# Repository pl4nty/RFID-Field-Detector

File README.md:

# RFID-Field-Detector  
  
## What is it?  
RFID-Field-Detector is an open source PCB the size of a credit card that is capable of detecting the field generated by a RFID reader and identify if it is a LF(125kHz) or HF/NFC(13.56MHz) reader.  
  
## Who made it, and why?  
Corey Harding, it is something neat to hand out to people, sort of like a business card.  
  
## How is it licensed?  
The hardware itself (KiCad and Fritzing files and Gerber) is licensed under Creative Commons Attribution-ShareAlike 3.0 Unported  
The SVG files fall under the MIT license  
  
## How can I modify it?  
Open `kicad/LF-HF-RFID-Detector.kicad_pro` in [KiCad](https://www.kicad.org/) 10 or later and modify whatever you wish provided you comply with the license stated above.  
The KiCad project was converted from `LF-HF-RFID-Detector.fzz`, which is kept for reference and can still be opened in Fritzing. The KiCad project has the PCB only; Fritzing's breadboard and schematic views were not converted.  
The place-file origin is the bottom-left corner of the board, as in Fritzing, so exported positions line up with `GERBER/positions.csv`.  
  
## Tuning  
Each antenna and its capacitors form a tuned circuit, and an LED only lights when the reader's frequency is near that circuit's resonance.  
- HF (13.56MHz): C6 (82pF) across the back coil (about 1.4uH). C7-C9 are left unfitted for small trims, e.g. a few pF. Do not fit nF parts here: 12nF across this coil tunes it to about 1.2MHz.  
- LF (125kHz): C1 and C2 in series, then C3-C5 in parallel, across the front coil (about 64uH). The fitted values total about 26nF, which tunes it to about 123kHz.  
  
## Will you help me?  
Maybe, but make sure you try first.  
  
## Is it available for sale?  
I have redesigned it as a commercial product and it is being manufactured and distributed by April Brother.  
Cost is sub $10.00 USD.  
Tindie: https://www.tindie.com/products/aprbrother/rfid-field-detector/

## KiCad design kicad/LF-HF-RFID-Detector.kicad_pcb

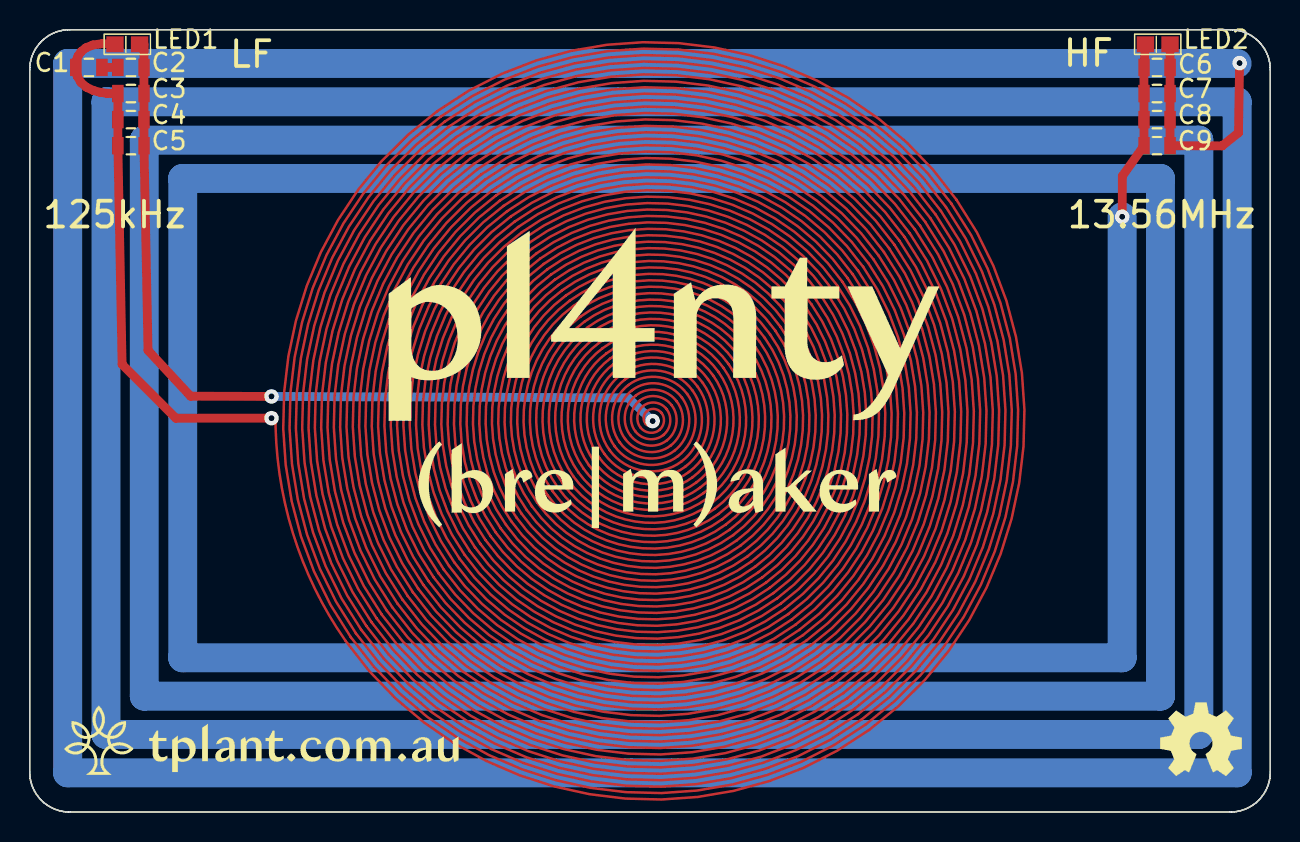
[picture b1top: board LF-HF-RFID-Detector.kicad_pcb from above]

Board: 2 copper layers, 85.6 x 54.0 mm, 11 parts (0 on the bottom side), 5 nets.

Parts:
C1, C2, C3, C4: 10nF; C_0805_Fritzing
C5: 1nF; C_0805_Fritzing
C6: 82pF; C_0805_Fritzing
C7, C8, C9: DNP; C_0805_Fritzing
LED1: APTD1608LSURCK; LED_0603_Fritzing
LED2: Green LED; LED_0603_Fritzing

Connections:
unnamed: C1.1, C3.1, C4.1, C5.1, LED1.1 (cathode)
unnamed: C1.2, C2.1
unnamed: C2.2, C3.2, C4.2, C5.2, LED1.2 (anode)
unnamed: C6.1, C7.1, C8.1, C9.1, LED2.1 (cathode)
unnamed: C6.2, C7.2, C8.2, C9.2, LED2.2 (anode)

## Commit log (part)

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2025-07-23 Rebrand, add PCBA artefacts
2025-07-29 Update BOM quantities
